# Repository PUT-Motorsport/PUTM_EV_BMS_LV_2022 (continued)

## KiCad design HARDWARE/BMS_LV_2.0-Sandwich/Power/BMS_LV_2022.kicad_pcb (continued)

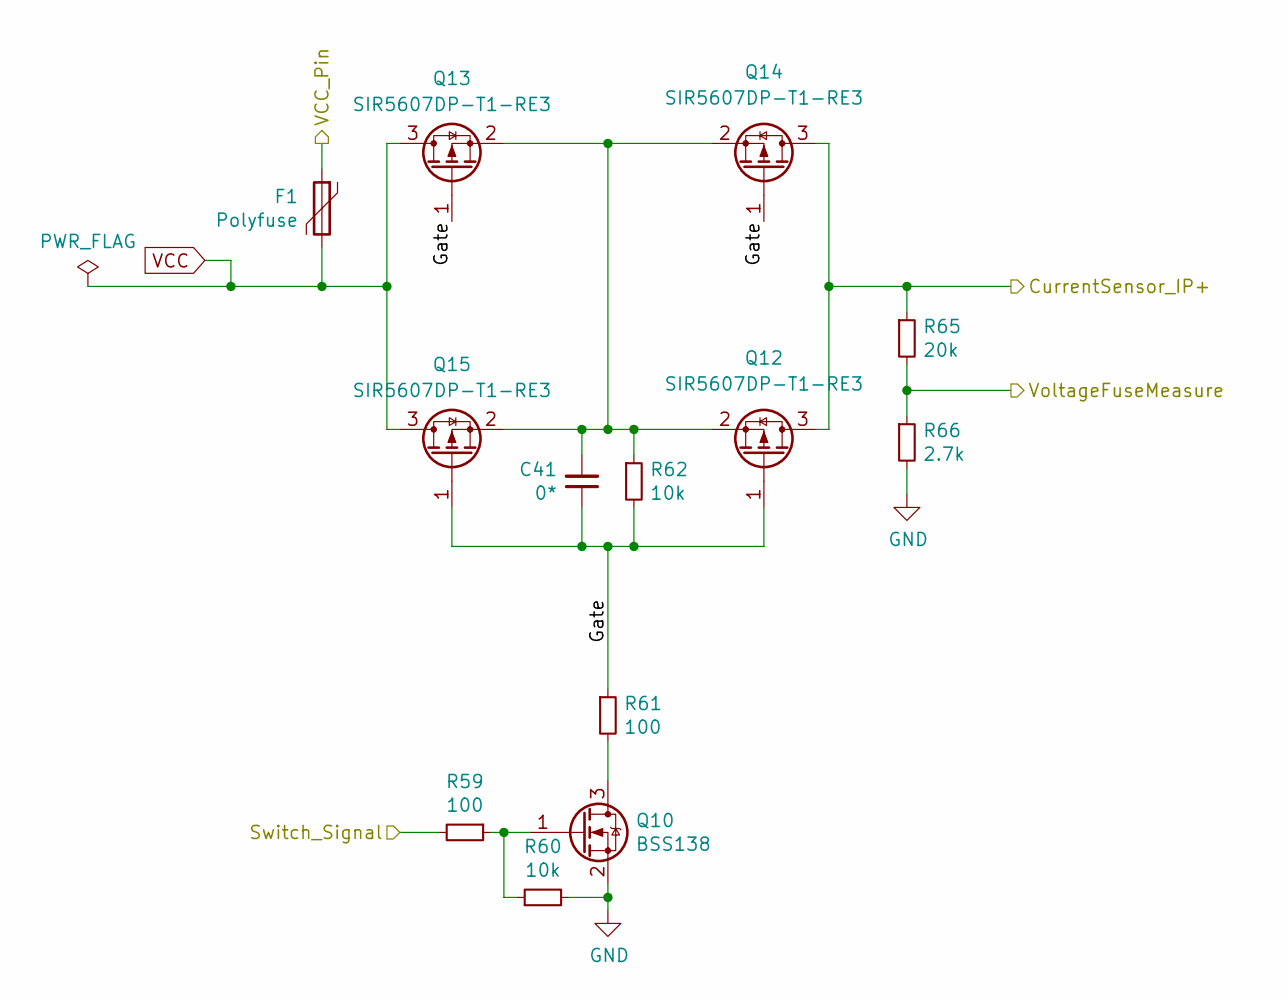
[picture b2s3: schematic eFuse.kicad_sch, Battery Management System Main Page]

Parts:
C41: 0*; C_0603_1608Metric
F1: Polyfuse; Fuse_1206_3216Metric; Part Number 0ZCJ0020FF2E
Q10: BSS138; SOT-23
Q12, Q13, Q14, Q15: SIR5607DP-T1-RE3
R59, R61: 100; R_0603_1608Metric
R60, R62: 10k; R_0603_1608Metric
R65: 20k; R_0603_1608Metric
R66: 2.7k; R_0603_1608Metric

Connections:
/CS_IP+: Q12.3 (D), Q14.3 (D), R65.1; also elsewhere on the board
/Switch_Signal: R59.2; also elsewhere on the board
/VCC_Pin: F1.1; also elsewhere on the board
/VoltageFuseMeasure: R65.2, R66.1; also elsewhere on the board
/eFuse/Gate: C41.1, Q12.1 (G), Q13.1 (G), Q14.1 (G), Q15.1 (G), R61.1, R62.2
GND: Q10.2 (S), R60.2, R66.2; also elsewhere on the board
unnamed: Q10.3 (D), R61.2
unnamed: Q10.1 (G), R59.1, R60.1
unnamed: C41.2, Q12.2 (S), Q13.2 (S), Q14.2 (S), Q15.2 (S), R62.1
VCC: F1.2, Q13.3 (D), Q15.3 (D); also elsewhere on the board

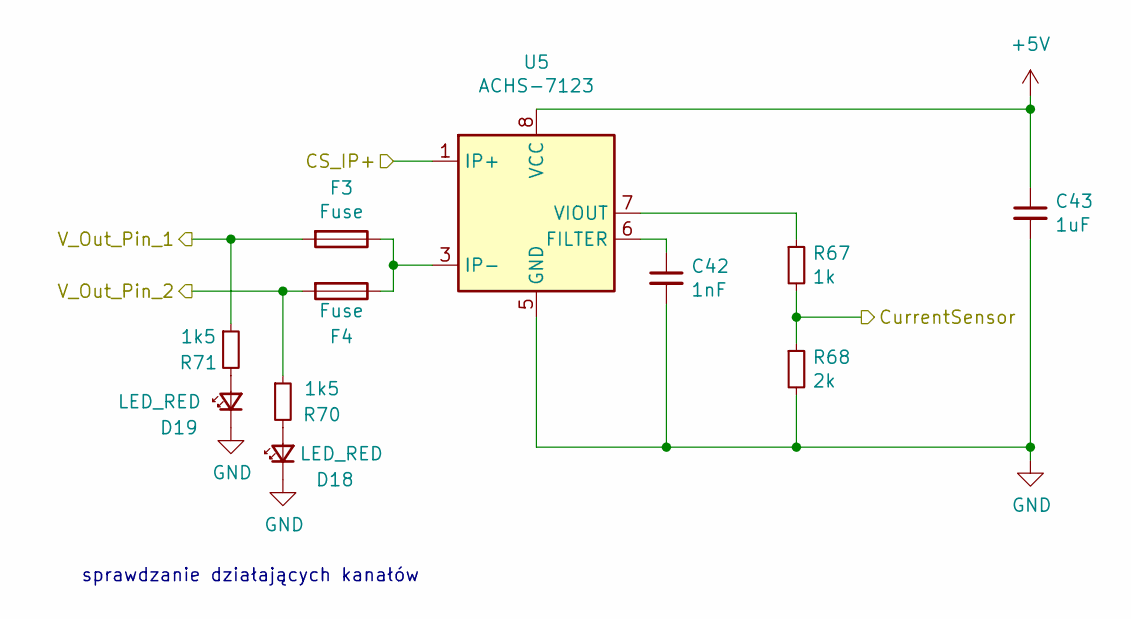
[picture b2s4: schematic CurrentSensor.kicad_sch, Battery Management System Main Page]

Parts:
C42: 1nF; C_0603_1608Metric
C43: 1uF; C_0603_1608Metric
D18, D19: LED_RED; LED_0603_1608Metric
F3, F4: Fuse; 01550900DR; Part Number 0680L9100-05
R67: 1k; R_0603_1608Metric
R68: 2k; R_0603_1608Metric
R70, R71: 1k5; R_0603_1608Metric
U5: ACHS-7123; SOIC-8_3.9x4.9mm_P1.27mm

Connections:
+5V: C43.1, U5.8 (VCC); also elsewhere on the board
/CS_IP+: U5.1 (IP+), U5.2 (IP+); also elsewhere on the board
/CurrentSensor_Out: R67.2, R68.1; also elsewhere on the board
/V_Out_Pin_1: F3.2, R71.1; also elsewhere on the board
/V_Out_Pin_2: F4.2, R70.1; also elsewhere on the board
GND: C42.2, C43.2, D18.1 (K), D19.1 (K), R68.2, U5.5 (GND); also elsewhere on the board
unnamed: D18.2 (A), R70.2
unnamed: D19.2 (A), R71.2
unnamed: F3.1, F4.1, U5.3 (IP-), U5.4 (IP-)
unnamed: C42.1, U5.6 (FILTER)
unnamed: R67.1, U5.7 (VIOUT)

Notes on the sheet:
sprawdzanie działających kanałów

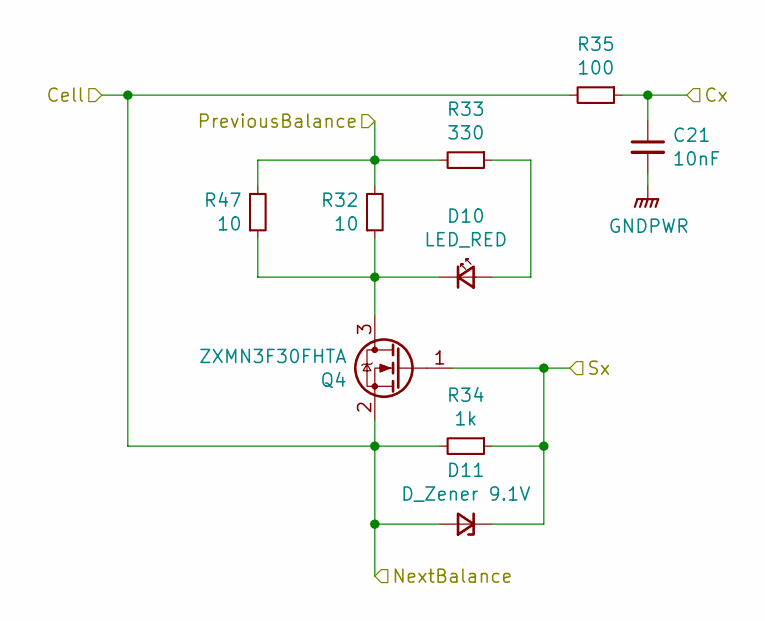
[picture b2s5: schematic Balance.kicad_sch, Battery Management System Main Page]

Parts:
C21: 10nF; C_0603_1608Metric
D10: LED_RED; LED_0603_1608Metric
D11: D_Zener 9.1V; D_SOD-323; Part Number BZX384-C9V1.115
Q4: ZXMN3F30FHTA; SOT-23
R32, R47: 10; RESC11050X120N; Mouser Part Number CHP2512AFX-10R0ELF
R33: 330; R_0603_1608Metric
R34: 1k; R_0603_1608Metric
R35: 100; R_0603_1608Metric

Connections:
/LTC6810/Balance3/Cx: C21.1, R35.1; also elsewhere on the board
/LTC6810/Balance3/Sx: D11.1 (K), Q4.1 (G), R34.1; also elsewhere on the board
/LTC6810/CellBalance3: R32.2, R33.2, R47.2; also elsewhere on the board
/LTC6810/CellBalance4: D11.2 (A), Q4.2 (S), R34.2, R35.2; also elsewhere on the board
GND: C21.2; also elsewhere on the board
unnamed: D10.2 (A), R33.1
unnamed: D10.1 (K), Q4.3 (D), R32.1, R47.1

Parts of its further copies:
C19, C20, C22, C23, C24: 10nF; C_0603_1608Metric
D6, D8, D12, D14, D16: LED_RED; LED_0603_1608Metric
D7, D9, D13, D15, D17: D_Zener 9.1V; D_SOD-323; Part Number BZX384-C9V1.115
Q2, Q3, Q5, Q6, Q7: ZXMN3F30FHTA; SOT-23
R23, R28, R37, R41, R57: 330; R_0603_1608Metric
R24, R29, R38, R43, R58: 1k; R_0603_1608Metric
R25, R30, R39, R44, R69: 100; R_0603_1608Metric
R27, R31, R36, R40, R42, R45, R46, R48, R49, R50: 10; RESC11050X120N; Mouser Part Number CHP2512AFX-10R0ELF

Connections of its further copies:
+BATT: R23.2, R27.2, R42.2; also elsewhere on the board
/LTC6810/Balance1/Cx: C19.1, R25.1; also elsewhere on the board
/LTC6810/Balance1/Sx: D7.1 (K), Q2.1 (G), R24.1; also elsewhere on the board
/LTC6810/Balance2/Cx: C20.1, R30.1; also elsewhere on the board
/LTC6810/Balance2/Sx: D9.1 (K), Q3.1 (G), R29.1; also elsewhere on the board
/LTC6810/Balance4/Cx: C22.1, R39.1; also elsewhere on the board
/LTC6810/Balance4/Sx: D13.1 (K), Q5.1 (G), R38.1; also elsewhere on the board
/LTC6810/Balance5/Cx: C23.1, R44.1; also elsewhere on the board
/LTC6810/Balance5/Sx: D15.1 (K), Q6.1 (G), R43.1; also elsewhere on the board
/LTC6810/Balance6/Cx: C24.1, R69.1; also elsewhere on the board
/LTC6810/Balance6/Sx: D17.1 (K), Q7.1 (G), R58.1; also elsewhere on the board
/LTC6810/CellBalance2: D7.2 (A), Q2.2 (S), R24.2, R25.2, R28.2, R31.2, R46.2; also elsewhere on the board
/LTC6810/CellBalance3: D9.2 (A), Q3.2 (S), R29.2, R30.2; also elsewhere on the board
/LTC6810/CellBalance4: R36.2, R37.2, R48.2; also elsewhere on the board
/LTC6810/CellBalance5: D13.2 (A), Q5.2 (S), R38.2, R39.2, R40.2, R41.2, R49.2; also elsewhere on the board
/LTC6810/CellBalance6: D15.2 (A), Q6.2 (S), R43.2, R44.2, R45.2, R50.2, R57.2; also elsewhere on the board
GND: C19.2, C20.2, C22.2, C23.2, C24.2, D17.2 (A), Q7.2 (S), R58.2, R69.2; also elsewhere on the board
unnamed: D6.2 (A), R23.1
unnamed: D6.1 (K), Q2.3 (D), R27.1, R42.1
unnamed: D8.2 (A), R28.1
unnamed: D8.1 (K), Q3.3 (D), R31.1, R46.1
unnamed: D12.2 (A), R37.1
unnamed: D12.1 (K), Q5.3 (D), R36.1, R48.1
unnamed: D14.2 (A), R41.1
unnamed: D14.1 (K), Q6.3 (D), R40.1, R49.1
unnamed: D16.2 (A), R57.1
unnamed: D16.1 (K), Q7.3 (D), R45.1, R50.1

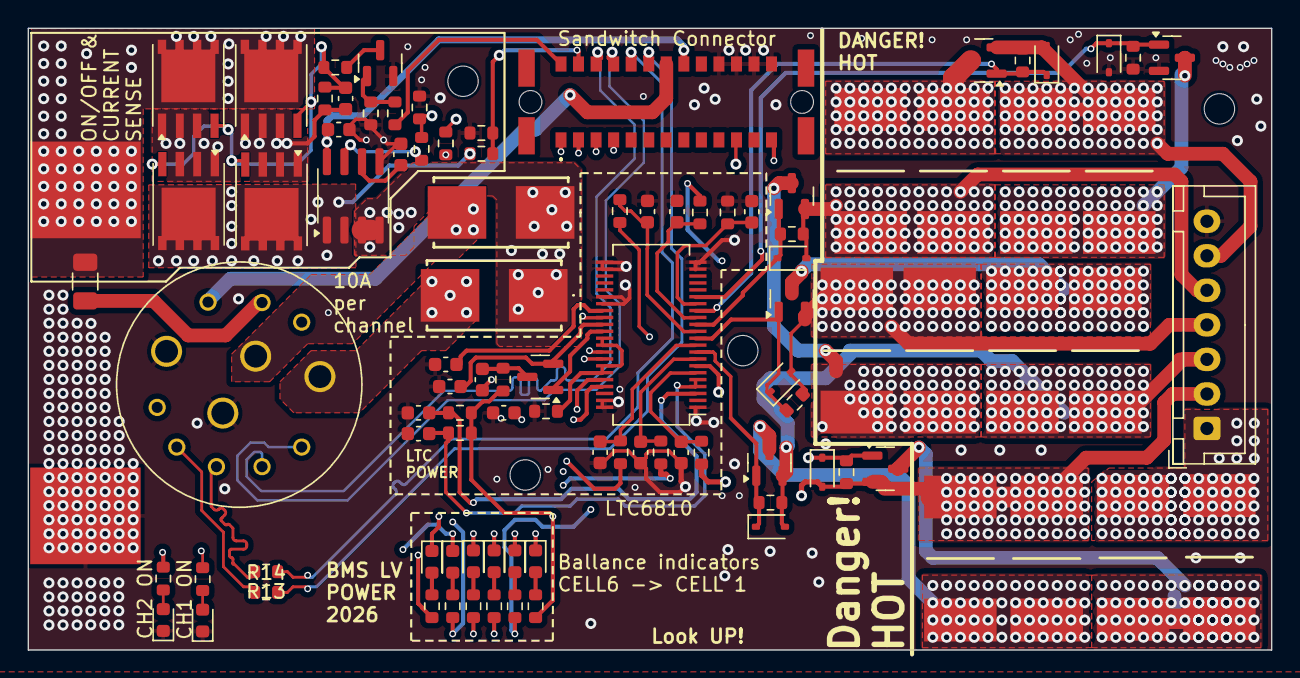
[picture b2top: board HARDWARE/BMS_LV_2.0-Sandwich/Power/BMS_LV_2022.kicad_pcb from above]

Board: 4 copper layers, 90.0 x 45.0 mm, 102 parts (1 on the bottom side), 70 nets.

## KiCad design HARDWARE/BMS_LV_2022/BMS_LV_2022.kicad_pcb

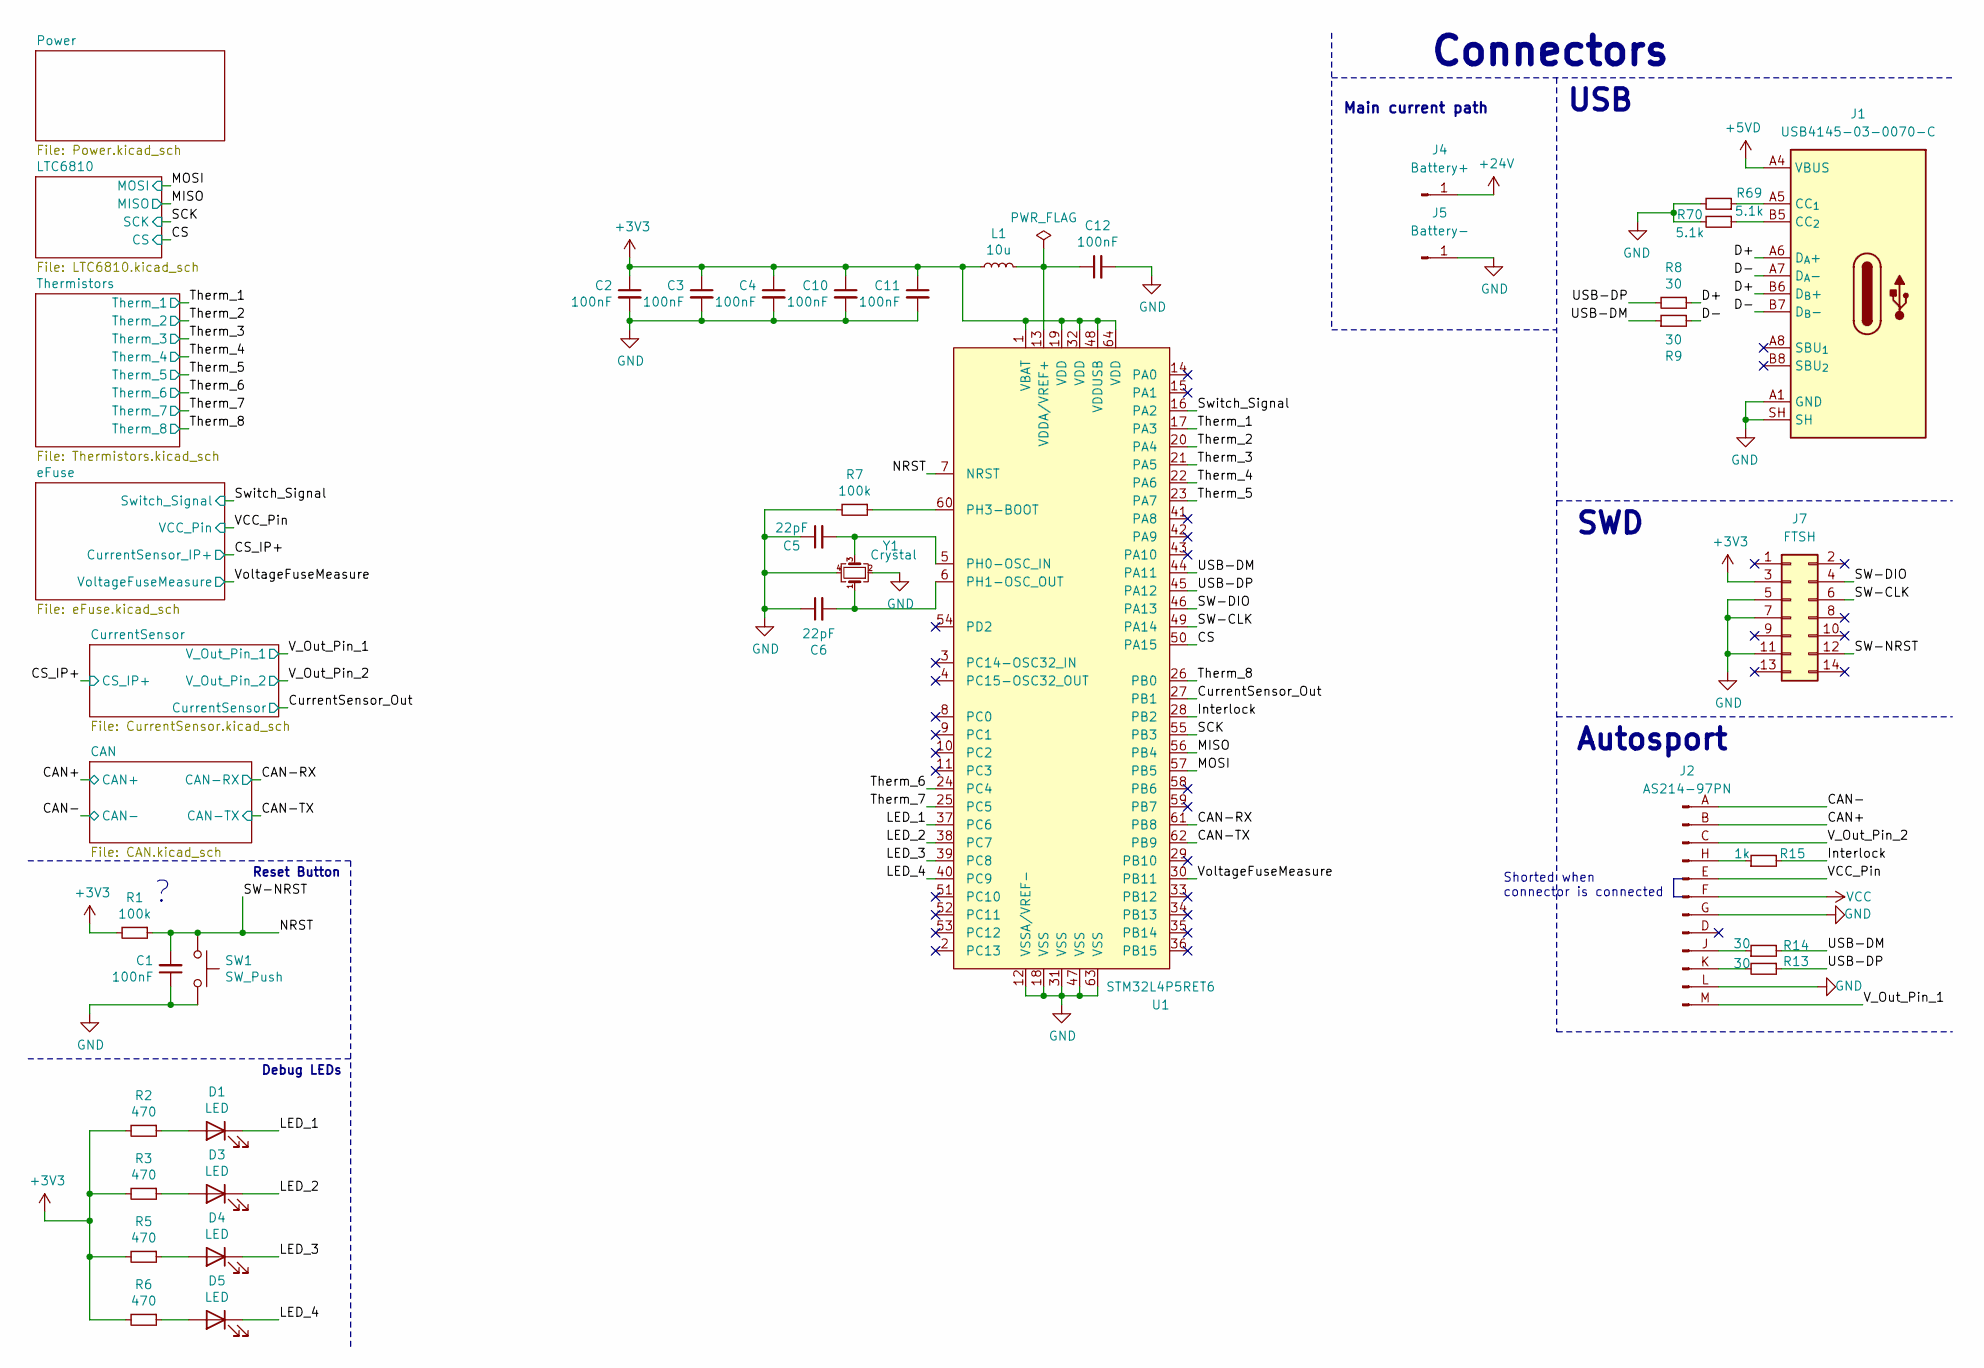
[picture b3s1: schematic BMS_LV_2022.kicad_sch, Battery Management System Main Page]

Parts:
C1, C2, C3, C4, C10, C11, C12: 100nF; C_0603_1608Metric
C5, C6: 22pF; C_0603_1608Metric
D1, D3, D4, D5: LED; LED_0603_1608Metric
J1: USB-C_GCT_USB4145-03-0070-C; USB-C_Receptacle_GCT_USB4145-03-0070-C; MPN USB4145-03-0070-C
J2: AS214-97PN
J4: Battery+; CellPad
J5: Battery-; CellPad
J7: FTSH; FTSH-107-XX-YYY-DV-K-A; Mouser Part Number 200-FTSH10701LDVKA
L1: 10u; L_0603_1608Metric
R1, R7: 100k; R_0603_1608Metric
R2, R3, R5, R6: 470; R_0603_1608Metric
R8, R9, R13, R14: 30; R_0603_1608Metric
R15: 1k; R_0603_1608Metric
R69, R70: 5.1k; R_0603_1608Metric
SW1: SW_Push; SW_SPST_B3U-1000P; Part Number B3U-1000PM
U1: STM32L4P5RET6; LQFP-64_10x10mm_P0.5mm
Y1: Crystal; Crystal_SMD_3225-4Pin_3.2x2.5mm

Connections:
+3V3: C2.1, C3.1, C4.1, C10.1, C11.1, J7.3, L1.2, R1.2, R2.2, R3.2, R5.2, R6.2, U1.1 (VBAT), U1.19 (VDD), U1.32 (VDD), U1.48 (VDDUSB), U1.64 (VDD); also elsewhere on the board
+5VD: J1.A4 (VBUS), J1.A9 (VBUS), J1.B4 (VBUS), J1.B9 (VBUS); also elsewhere on the board
+24V: J4.1; also elsewhere on the board
/CAN+: J2.B; also elsewhere on the board
/CAN-: J2.A; also elsewhere on the board
/CAN-RX: U1.61 (PB8); also elsewhere on the board
/CAN-TX: U1.62 (PB9); also elsewhere on the board
/CS: U1.50 (PA15); also elsewhere on the board
/CurrentSensor_Out: U1.27 (PB1); also elsewhere on the board
/D+: J1.A6 (D_{A}+), J1.B6 (D_{B}+), R8.1
/D-: J1.A7 (D_{A}-), J1.B7 (D_{B}-), R9.2
/Interlock: R15.2, U1.28 (PB2)
/LED_1: D1.1 (K), U1.37 (PC6)
/LED_2: D3.1 (K), U1.38 (PC7)
/LED_3: D4.1 (K), U1.39 (PC8)
/LED_4: D5.1 (K), U1.40 (PC9)
/MISO: U1.56 (PB4); also elsewhere on the board
/MOSI: U1.57 (PB5); also elsewhere on the board
/NRST: C1.2, J7.12, R1.1, SW1.1, U1.7 (NRST)
/SCK: U1.55 (PB3); also elsewhere on the board
/SW-CLK: J7.6, U1.49 (PA14)
/SW-DIO: J7.4, U1.46 (PA13)
/Switch_Signal: U1.16 (PA2); also elsewhere on the board
/Therm_1: U1.17 (PA3); also elsewhere on the board
/Therm_2: U1.20 (PA4); also elsewhere on the board
/Therm_3: U1.21 (PA5); also elsewhere on the board
/Therm_4: U1.22 (PA6); also elsewhere on the board
/Therm_5: U1.23 (PA7); also elsewhere on the board
/Therm_6: U1.24 (PC4); also elsewhere on the board
/Therm_7: U1.25 (PC5); also elsewhere on the board
/Therm_8: U1.26 (PB0); also elsewhere on the board
/USB-DM: R9.1, R14.2, U1.44 (PA11)
/USB-DP: R8.2, R13.1, U1.45 (PA12)
/VCC_Pin: J2.E; also elsewhere on the board
/V_Out_Pin_1: J2.M; also elsewhere on the board
/V_Out_Pin_2: J2.C; also elsewhere on the board
/VoltageFuseMeasure: U1.30 (PB11); also elsewhere on the board
GND: C1.1, C2.2, C3.2, C4.2, C5.1, C6.1, C10.2, C11.2, C12.2, J1.A1 (GND), J1.A12 (GND), J1.B1 (GND), J1.B12 (GND), J1.SH, J2.G, J2.L, J5.1, J7.5, J7.7, J7.11, R7.2, R69.2, R70.2, SW1.2, U1.12 (VSSA/VREF-), U1.18 (VSS), U1.31 (VSS), U1.47 (VSS), U1.63 (VSS), Y1.2, Y1.4; also elsewhere on the board
unnamed: D1.2 (A), R2.1
unnamed: D3.2 (A), R3.1
unnamed: D4.2 (A), R5.1
unnamed: D5.2 (A), R6.1
unnamed: J1.A5 (CC_{1}), R69.1
unnamed: J1.B5 (CC_{2}), R70.1
unnamed: J2.H, R15.1
unnamed: J2.J, R14.1
unnamed: J2.K, R13.2
unnamed: C5.2, U1.5 (PH0-OSC_IN), Y1.3
unnamed: C6.2, U1.6 (PH1-OSC_OUT), Y1.1
unnamed: R7.1, U1.60 (PH3-BOOT)
unnamed: C12.1, L1.1, U1.13 (VDDA/VREF+)
VCC: J2.F; also elsewhere on the board

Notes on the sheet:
SWD
USB
Debug LEDs
Reset Button
Main current path
Shorted when connector is connected
Connectors
Autosport

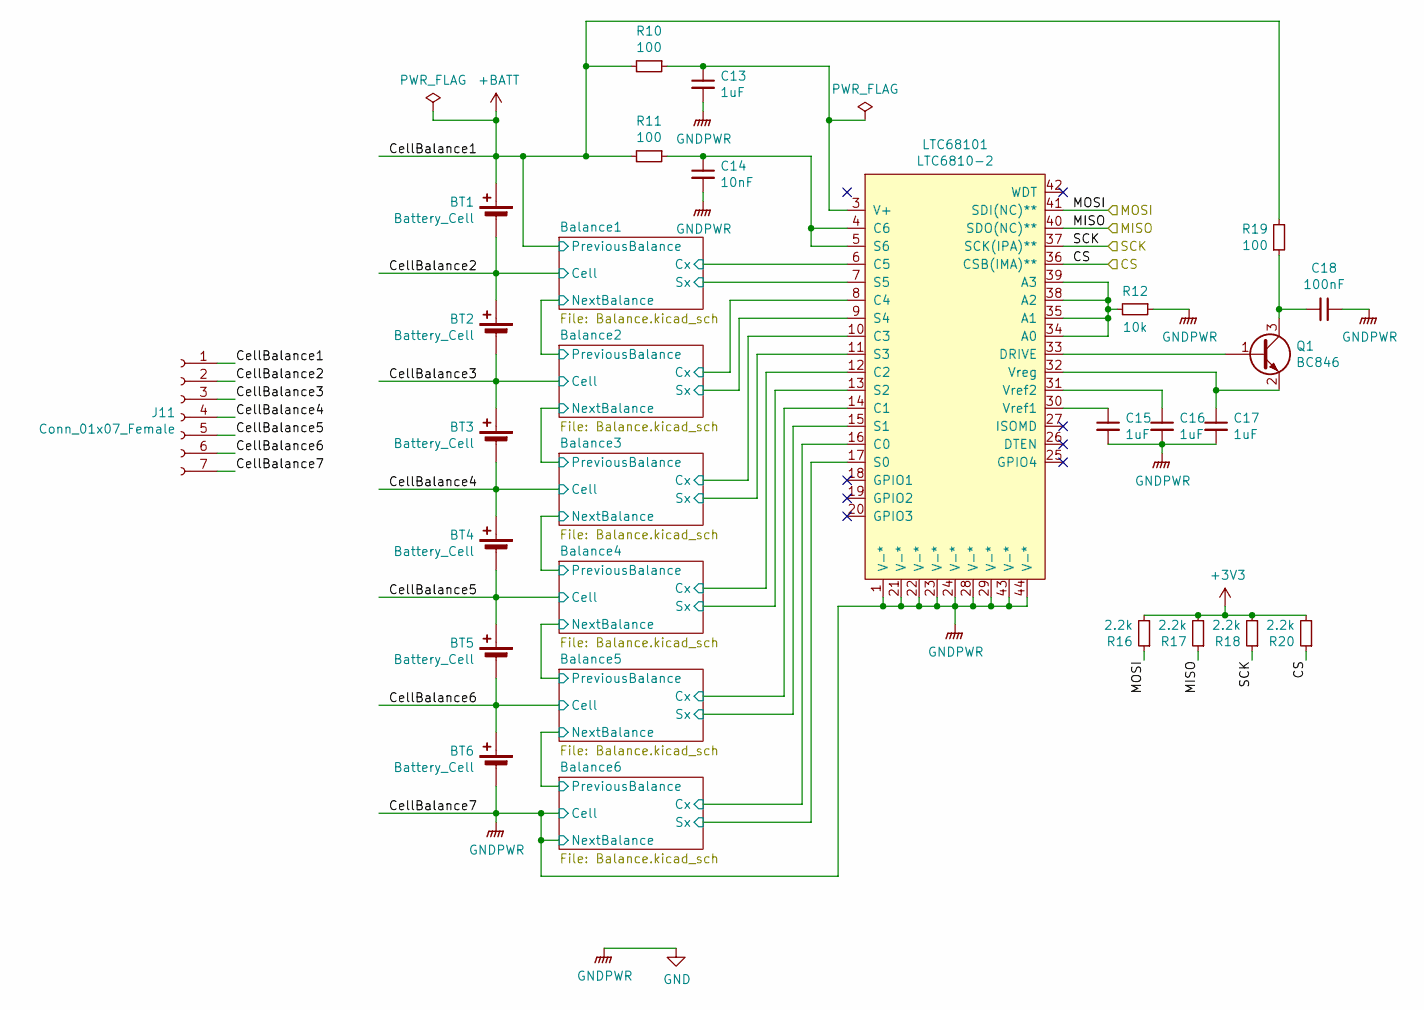
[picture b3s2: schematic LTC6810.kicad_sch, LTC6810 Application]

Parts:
BT1, BT2, BT3, BT4, BT5, BT6: Battery_Cell
C13, C15, C16, C17: 1uF; C_0603_1608Metric
C14: 10nF; C_0603_1608Metric
C18: 100nF; C_0603_1608Metric
J11: Conn_01x07_Female; JST_XH_B7B-XH-A_1x07_P2.50mm_Vertical
LTC68101: LTC6810-2; LTC6810
Q1: BC846; SOT-23
R10, R11, R19: 100; R_0603_1608Metric
R12: 10k; R_0603_1608Metric
R16, R17, R18, R20: 2.2k; R_0603_1608Metric

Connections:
+3V3: R16.2, R17.2, R18.2, R20.2; also elsewhere on the board
+BATT: BT1.1 (+), J11.1, R10.2, R11.2, R19.2; also elsewhere on the board
/CS: LTC68101.36 (CSB(IMA)**), R20.1; also elsewhere on the board
/LTC6810/Balance1/Cx: LTC68101.6 (C5); also elsewhere on the board
/LTC6810/Balance1/Sx: LTC68101.7 (S5); also elsewhere on the board
/LTC6810/Balance2/Cx: LTC68101.8 (C4); also elsewhere on the board
/LTC6810/Balance2/Sx: LTC68101.9 (S4); also elsewhere on the board
/LTC6810/Balance3/Cx: LTC68101.10 (C3); also elsewhere on the board
/LTC6810/Balance3/Sx: LTC68101.11 (S3); also elsewhere on the board
/LTC6810/Balance4/Cx: LTC68101.12 (C2); also elsewhere on the board
/LTC6810/Balance4/Sx: LTC68101.13 (S2); also elsewhere on the board
/LTC6810/Balance5/Cx: LTC68101.14 (C1); also elsewhere on the board
/LTC6810/Balance5/Sx: LTC68101.15 (S1); also elsewhere on the board
/LTC6810/Balance6/Cx: LTC68101.16 (C0); also elsewhere on the board
/LTC6810/Balance6/Sx: LTC68101.17 (S0); also elsewhere on the board
/LTC6810/CellBalance2: BT1.2 (-), BT2.1 (+), J11.2; also elsewhere on the board
/LTC6810/CellBalance3: BT2.2 (-), BT3.1 (+), J11.3; also elsewhere on the board
/LTC6810/CellBalance4: BT3.2 (-), BT4.1 (+), J11.4; also elsewhere on the board
/LTC6810/CellBalance5: BT4.2 (-), BT5.1 (+), J11.5; also elsewhere on the board
/LTC6810/CellBalance6: BT5.2 (-), BT6.1 (+), J11.6; also elsewhere on the board
/MISO: LTC68101.40 (SDO(NC)**), R17.1; also elsewhere on the board
/MOSI: LTC68101.41 (SDI(NC)**), R16.1; also elsewhere on the board
/SCK: LTC68101.37 (SCK(IPA)**), R18.1; also elsewhere on the board
GND: BT6.2 (-), C13.2, C14.2, C15.2, C16.2, C17.2, C18.1, J11.7, LTC68101.1 (V-*), LTC68101.21 (V-*), LTC68101.22 (V-*), LTC68101.23 (V-*), LTC68101.24 (V-*), LTC68101.28 (V-*), LTC68101.29 (V-*), LTC68101.43 (V-*), LTC68101.44 (V-*), R12.1; also elsewhere on the board
unnamed: LTC68101.34 (A0), LTC68101.35 (A1), LTC68101.38 (A2), LTC68101.39 (A3), R12.2
unnamed: C14.1, LTC68101.4 (C6), LTC68101.5 (S6), R11.1
unnamed: LTC68101.33 (DRIVE), Q1.1 (B)
unnamed: C13.1, LTC68101.3 (V+), R10.1
unnamed: C15.1, LTC68101.30 (Vref1)
unnamed: C16.1, LTC68101.31 (Vref2)
unnamed: C17.1, LTC68101.32 (Vreg), Q1.2 (E)
unnamed: C18.2, Q1.3 (C), R19.1

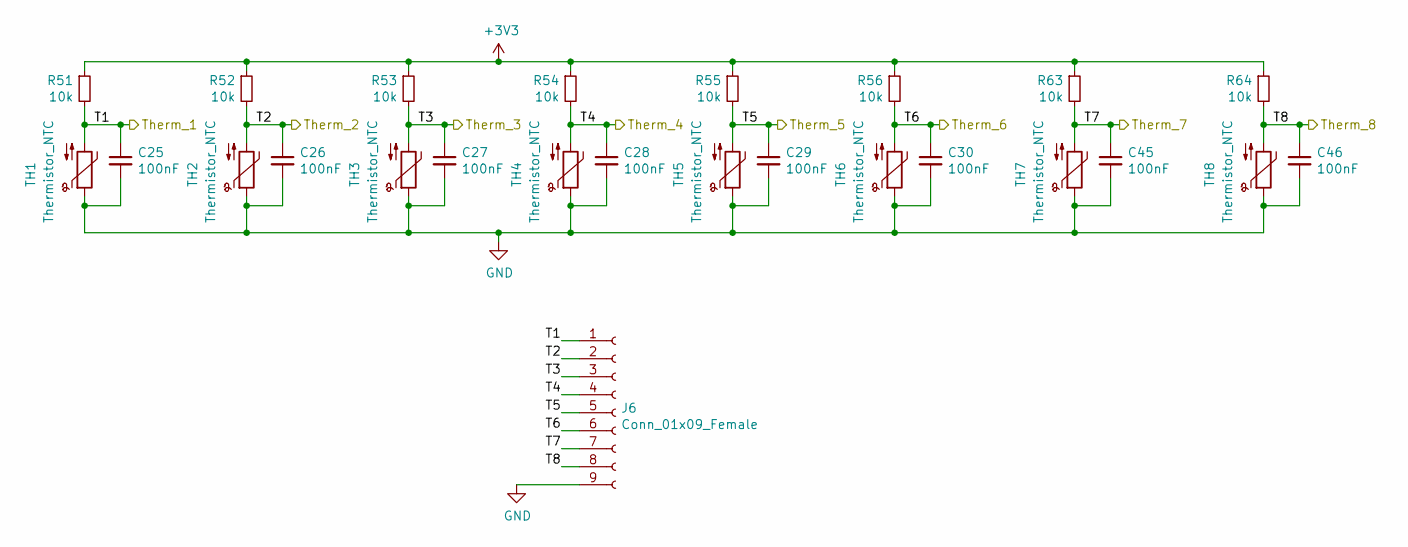
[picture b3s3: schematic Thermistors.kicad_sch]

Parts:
C25, C26, C27, C28, C29, C30, C45, C46: 100nF; C_0603_1608Metric
J6: Conn_01x09_Female; JST_XH_B9B-XH-A_1x09_P2.50mm_Vertical
R51, R52, R53, R54, R55, R56, R63, R64: 10k; R_0603_1608Metric
TH1, TH2, TH3, TH4, TH5, TH6, TH7, TH8: Thermistor_NTC

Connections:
+3V3: R51.1, R52.1, R53.1, R54.1, R55.1, R56.1, R63.1, R64.1; also elsewhere on the board
/Therm_1: C25.1, J6.1, R51.2, TH1.2; also elsewhere on the board
/Therm_2: C26.1, J6.2, R52.2, TH2.2; also elsewhere on the board
/Therm_3: C27.1, J6.3, R53.2, TH3.2; also elsewhere on the board
/Therm_4: C28.1, J6.4, R54.2, TH4.2; also elsewhere on the board
/Therm_5: C29.1, J6.5, R55.2, TH5.2; also elsewhere on the board
/Therm_6: C30.1, J6.6, R56.2, TH6.2; also elsewhere on the board
/Therm_7: C45.1, J6.7, R63.2, TH7.2; also elsewhere on the board
/Therm_8: C46.1, J6.8, R64.2, TH8.2; also elsewhere on the board
GND: C25.2, C26.2, C27.2, C28.2, C29.2, C30.2, C45.2, C46.2, J6.9, TH1.1, TH2.1, TH3.1, TH4.1, TH5.1, TH6.1, TH7.1, TH8.1; also elsewhere on the board

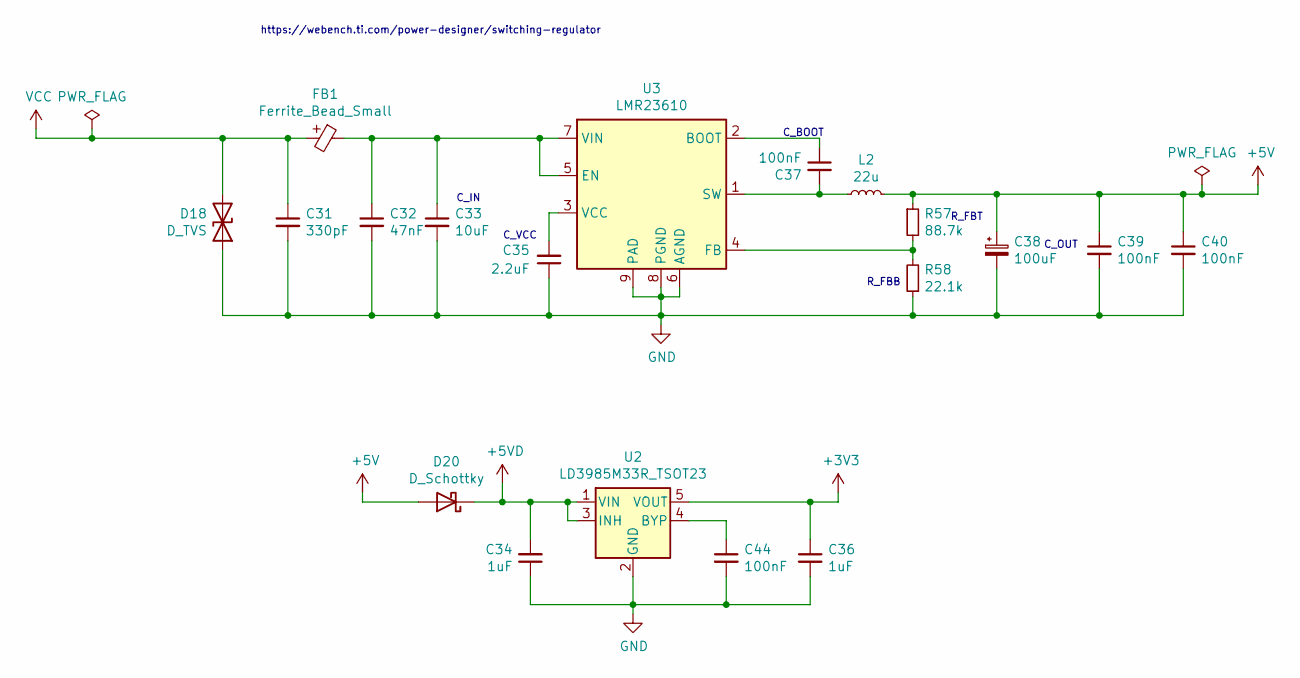
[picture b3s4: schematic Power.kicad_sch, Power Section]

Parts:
C31: 330pF; C_0603_1608Metric
C32: 47nF; C_0603_1608Metric
C33: 10uF; C_0603_1608Metric
C34, C36: 1uF; C_0603_1608Metric
C35: 2.2uF; C_0603_1608Metric
C37, C39, C40, C44: 100nF; C_0603_1608Metric
C38: 100uF; CP_EIA-6032-28_Kemet-C; Part Number TPSC107K010R0100
D18: D_TVS; D_SMB
D20: D_Schottky; D_SOD-123; Part Number SD103BW
FB1: Ferrite_Bead_Small; L_0603_1608Metric
L2: 22u; L_7.3x7.3_H4.5; Part Number 7447779122
R57: 88.7k; R_0603_1608Metric
R58: 22.1k; R_0603_1608Metric
U2: LD3985M33R_TSOT23; TSOT-23-5; Part Number LDS3985M33R
U3: LMR23610; Texas_HSOP-8-1EP_3.9x4.9mm_P1.27mm_ThermalVias

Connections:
+3V3: C36.1, U2.5 (VOUT); also elsewhere on the board
+5V: C38.1, C39.1, C40.1, D20.2 (A), L2.2, R57.1; also elsewhere on the board
+5VD: C34.2, D20.1 (K), U2.1 (VIN), U2.3 (INH); also elsewhere on the board
GND: C31.2, C32.2, C33.2, C34.1, C35.1, C36.2, C38.2, C39.2, C40.2, C44.2, D18.1 (A1), R58.1, U2.2 (GND), U3.6 (AGND), U3.8 (PGND), U3.9 (PAD); also elsewhere on the board
unnamed: C44.1, U2.4 (BYP)
unnamed: C37.1, U3.2 (BOOT)
unnamed: C32.1, C33.1, FB1.1, U3.5 (EN), U3.7 (VIN)
unnamed: R57.2, R58.2, U3.4 (FB)
unnamed: C37.2, L2.1, U3.1 (SW)
unnamed: C35.2, U3.3 (VCC)
VCC: C31.1, D18.2 (A2), FB1.2; also elsewhere on the board

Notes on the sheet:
C_BOOT
https://webench.ti.com/power-designer/switching-regulator
C_IN
R_FBB
R_FBT
C_VCC
C_OUT

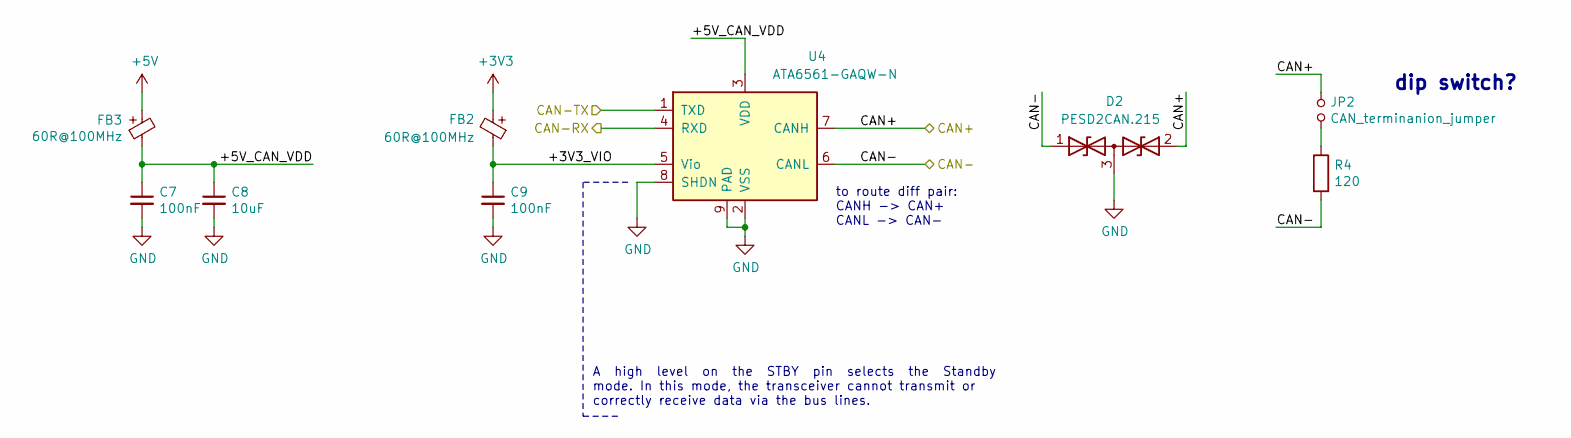
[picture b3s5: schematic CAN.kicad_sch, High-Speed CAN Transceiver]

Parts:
C7, C9: 100nF; C_0603_1608Metric
C8: 10uF; C_0603_1608Metric
D2: PESD2CAN.215; SOT-23
FB2, FB3: 60R@100MHz; L_0603_1608Metric
JP2: CAN_terminanion_jumper; SolderJumper-2_P1.3mm_Open_TrianglePad1.0x1.5mm
R4: 120; R_0603_1608Metric
U4: ATA6561-GAQW-N; SOIC-8_3.9x4.9mm_P1.27mm

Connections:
+3V3: FB2.2; also elsewhere on the board
+5V: FB3.2; also elsewhere on the board
/CAN+: D2.2 (A2), JP2.1, U4.7 (CANH); also elsewhere on the board
/CAN-: D2.1 (A1), R4.2, U4.6 (CANL); also elsewhere on the board
/CAN-RX: U4.4 (RXD); also elsewhere on the board
/CAN-TX: U4.1 (TXD); also elsewhere on the board
/CAN/+3V3_VIO: C9.1, FB2.1, U4.5 (Vio)
/CAN/+5V_CAN_VDD: C7.1, C8.1, FB3.1, U4.3 (VDD)
GND: C7.2, C8.2, C9.2, D2.3 (common), U4.2 (VSS), U4.8 (SHDN), U4.9 (PAD); also elsewhere on the board
unnamed: JP2.2, R4.1

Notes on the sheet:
dip switch?
A high level on the STBY pin selects the Standby mode. In this mode, the transceiver cannot transmit or correctly receive data via the bus lines.
to route diff pair: CANH -> CAN+ CANL -> CAN-

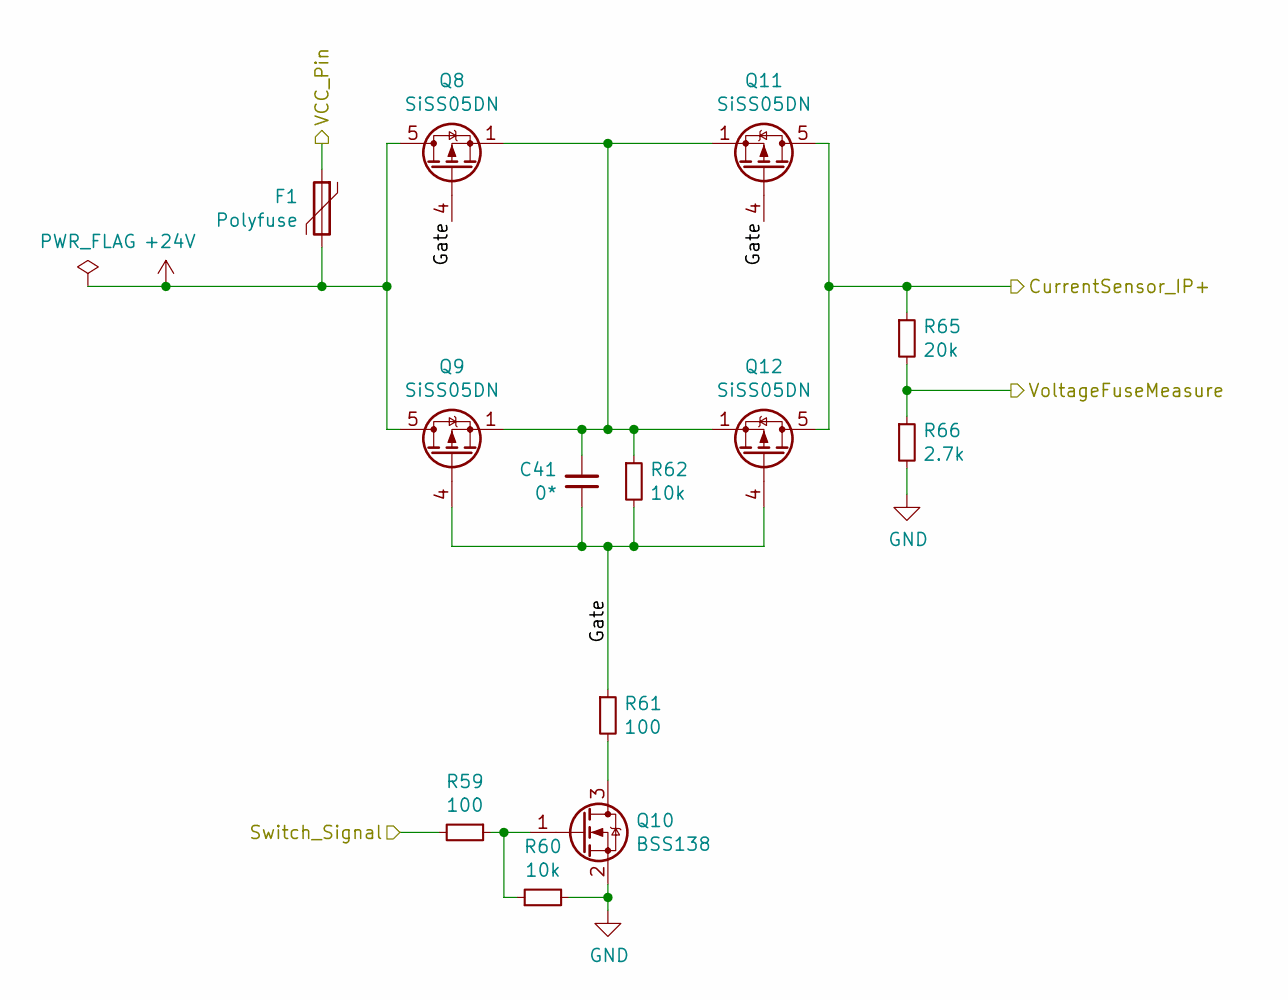
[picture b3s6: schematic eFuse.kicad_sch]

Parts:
C41: 0*; C_0603_1608Metric
F1: Polyfuse; Fuse_1206_3216Metric; Part Number 0ZCJ0020FF2E
Q8, Q9, Q11, Q12: SiSS05DN; Vishay_PowerPAK_1212-8_Single; Part Number SISS05DN-T1-GE3
Q10: BSS138; SOT-23
R59, R61: 100; R_0603_1608Metric
R60, R62: 10k; R_0603_1608Metric
R65: 20k; R_0603_1608Metric
R66: 2.7k; R_0603_1608Metric

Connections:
+24V: F1.2, Q8.5 (D), Q9.5 (D); also elsewhere on the board
/CS_IP+: Q11.5 (D), Q12.5 (D), R65.1; also elsewhere on the board
/Switch_Signal: R59.2; also elsewhere on the board
/VCC_Pin: F1.1; also elsewhere on the board
/VoltageFuseMeasure: R65.2, R66.1; also elsewhere on the board
/eFuse/Gate: C41.1, Q8.4 (G), Q9.4 (G), Q11.4 (G), Q12.4 (G), R61.1, R62.2
GND: Q10.2 (S), R60.2, R66.2; also elsewhere on the board
unnamed: C41.2, Q8.1 (S), Q8.2 (S), Q8.3 (S), Q9.1 (S), Q9.2 (S), Q9.3 (S), Q11.1 (S), Q11.2 (S), Q11.3 (S), Q12.1 (S), Q12.2 (S), Q12.3 (S), R62.1
unnamed: Q10.3 (D), R61.2
unnamed: Q10.1 (G), R59.1, R60.1

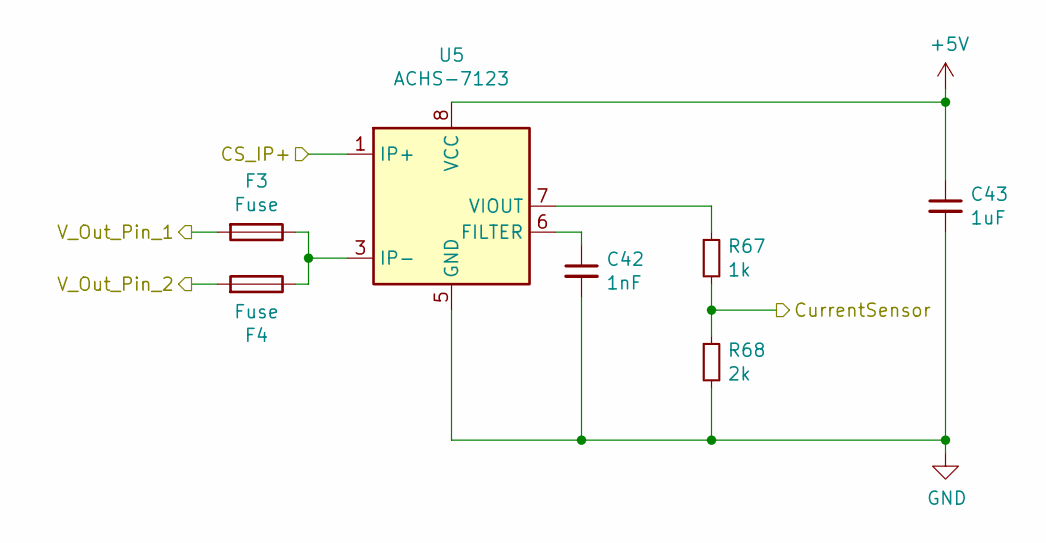
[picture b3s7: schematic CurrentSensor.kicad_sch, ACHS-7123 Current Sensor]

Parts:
C42: 1nF; C_0603_1608Metric
C43: 1uF; C_0603_1608Metric
F3, F4: Fuse; 0154001.DRT; Part Number 0154010.DR
R67: 1k; R_0603_1608Metric
R68: 2k; R_0603_1608Metric
U5: ACHS-7123; SOIC-8_3.9x4.9mm_P1.27mm

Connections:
+5V: C43.1, U5.8 (VCC); also elsewhere on the board
/CS_IP+: U5.1 (IP+), U5.2 (IP+); also elsewhere on the board
/CurrentSensor_Out: R67.2, R68.1; also elsewhere on the board
/V_Out_Pin_1: F3.2; also elsewhere on the board
/V_Out_Pin_2: F4.2; also elsewhere on the board
GND: C42.2, C43.2, R68.2, U5.5 (GND); also elsewhere on the board
unnamed: F3.1, F4.1, U5.3 (IP-), U5.4 (IP-)
unnamed: C42.1, U5.6 (FILTER)
unnamed: R67.1, U5.7 (VIOUT)
